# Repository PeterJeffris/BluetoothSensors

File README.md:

Background:
The goal of this project is to create an sensor platform wirelessly connected to a control and logging application on an android phone. The sensors include an accelerometer, a gyroscope, a combined barometer and temperature sensor and an ambient light sensor. The data is logged to the phones internal SD card or simply shown on the screen set with GUI configuration buttons on the android phone.

Software Development:
There are 3 collections of software developed for this project. The first is the java code for the android phone residing in the android folder. This code is intended to be compiled and uploaded to the phone using the android SDK package in the Eclipse IDE. This code contains a multithreaded android application that manages the display and configuration options in one group of threads and receives and processes and logs the data received over the Bluetooth radio connection in the other set.

The second collection of code is written in C++ and is used to run the Atmega328 chip that coordinates the collection of data from the sensors and is found in the AVR folder. This code is meant to be used with the wiring libraries and can be uploaded via the Arduino IDE or a build program such as scons or make. I2C driver libraries were written for this application to communicate with each of the sensors and are also included in this folder. Additionally there is a test script written in python that allows direct collection from the senor board by hooking up an FTDI cable to the Tx and Rx lines of the radio.

The final code is written in matlab and is used to determine the calibration coefficients for the relative alignment and scaling of the accelerometer and gyroscope. There are also several functions written to perform conversions between Euler angles which the gyroscope returns and rotation matrix and quaternion representations.

Hardware Development:
The circuit schematics and PCB layout are present in the hardware folder. These files are mean to be developed with the Eagle CAD software. The board itself is constructed as an Arduino compatible shield and matches directly with the pins on an Arduino board. Each of the sensors was purchased on breakout boards from sparkfun allowing for through hole construction techniques using chemically etched boards. 

A solder jumper had to be modified on the bottom of the gyroscope boards in order to change their output from SPI to I2C. Along with the gyroscope, the accelerometer and barometer also use the I2C communication protocol. Theses chips are placed on a single BUS with 3.3 Volt logic. This logic is then converted to 5 volt logic to the AVR processor using a level shifting circuit. The power supply utilizes 4 AA alkaline batteries whose voltage begins at 5.6 volts and drops to 4 volts at 4 discharge. The linear regulator supply filters and regulates this voltage at the cost of a 1 volt drop out. The AVR processor and radio are tolerant to the voltage changes down to the point where the batteries are operating at 4 volts. 

To configure the radio it must be connected to an FTDI cable. Open a serial terminal using the FTDI port (the arduino IDE serial monitor will also work if you select the FTDI port) and disable the line ending on output and send the string '$$$' (everything inside '' is entered and return is pressed). You will see the radio enter command mode by returning 'CMD' if you have done the setup correctly and the status light will blink at a faster interval. Then re-enable line endings and send the command 'SN,DEVICE_NAME' where DEVICE_NAME is what you want the bluetooth device name to be displayed as. Use the command 'SP,XXXX' to set the security pin where XXXX is the alphanumeric pin code to be entered upon connecting to the device from a phone. Use the command 'SU,XX' to set the baud rate where the XX is the first two characters of the baud rate (ie 11 -> 115000 bits per second). If this is done the corresponding baud rate in the AVR code also needs to be changed. To verify this information has been properly set use the 'D' command to display the basic settings. 

Features: 
The slides included in this repository describe the various features of the system and show the conclusions of the experimental trials utilizing the sensor.

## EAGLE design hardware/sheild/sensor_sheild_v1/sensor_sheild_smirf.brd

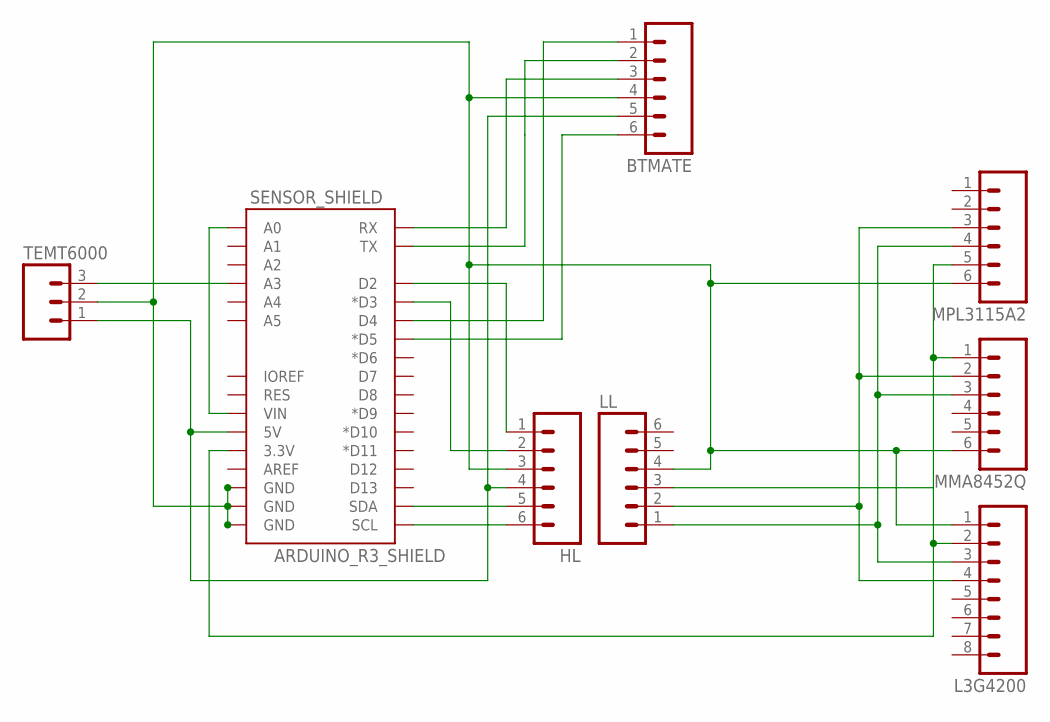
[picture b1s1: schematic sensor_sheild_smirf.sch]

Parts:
BTMATE: M06NO_SILK; 1X06_NO_SILK
HL: M06SIP; 1X06
L3G4200: M08; 1X08_PIN1_NO_SILK
LL: M06SIP; 1X06
MMA8452Q: M06SIP; 1X06
MPL3115A2: M06SIP; 1X06
SENSOR_SHIELD: ARDUINO_R3_SHIELD; UNO_R3_SHIELD
TEMT6000: M031X03_NO_SILK; 1X03_NO_SILK

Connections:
GND: BTMATE.4, HL.3, L3G4200.1, LL.4, MMA8452Q.6, MPL3115A2.6, SENSOR_SHIELD.GND@0 (GND), SENSOR_SHIELD.GND@1 (GND), SENSOR_SHIELD.GND@2 (GND), TEMT6000.2
unnamed: SENSOR_SHIELD.A0, SENSOR_SHIELD.VIN
unnamed: BTMATE.2, SENSOR_SHIELD.TX
unnamed: BTMATE.3, SENSOR_SHIELD.RX
unnamed: BTMATE.1, SENSOR_SHIELD.D4
unnamed: BTMATE.6, SENSOR_SHIELD.D5 (*D5)
unnamed: L3G4200.4, LL.2, MMA8452Q.2, MPL3115A2.3
unnamed: HL.2, SENSOR_SHIELD.D3 (*D3)
unnamed: HL.1, SENSOR_SHIELD.D2
unnamed: L3G4200.3, LL.1, MMA8452Q.3, MPL3115A2.4
unnamed: HL.5, SENSOR_SHIELD.SDA
unnamed: BTMATE.5, HL.4, SENSOR_SHIELD.5V, TEMT6000.1
unnamed: L3G4200.2, LL.3, MMA8452Q.1, MPL3115A2.5, SENSOR_SHIELD.3.3V
unnamed: HL.6, SENSOR_SHIELD.SCL
unnamed: SENSOR_SHIELD.A3, TEMT6000.3

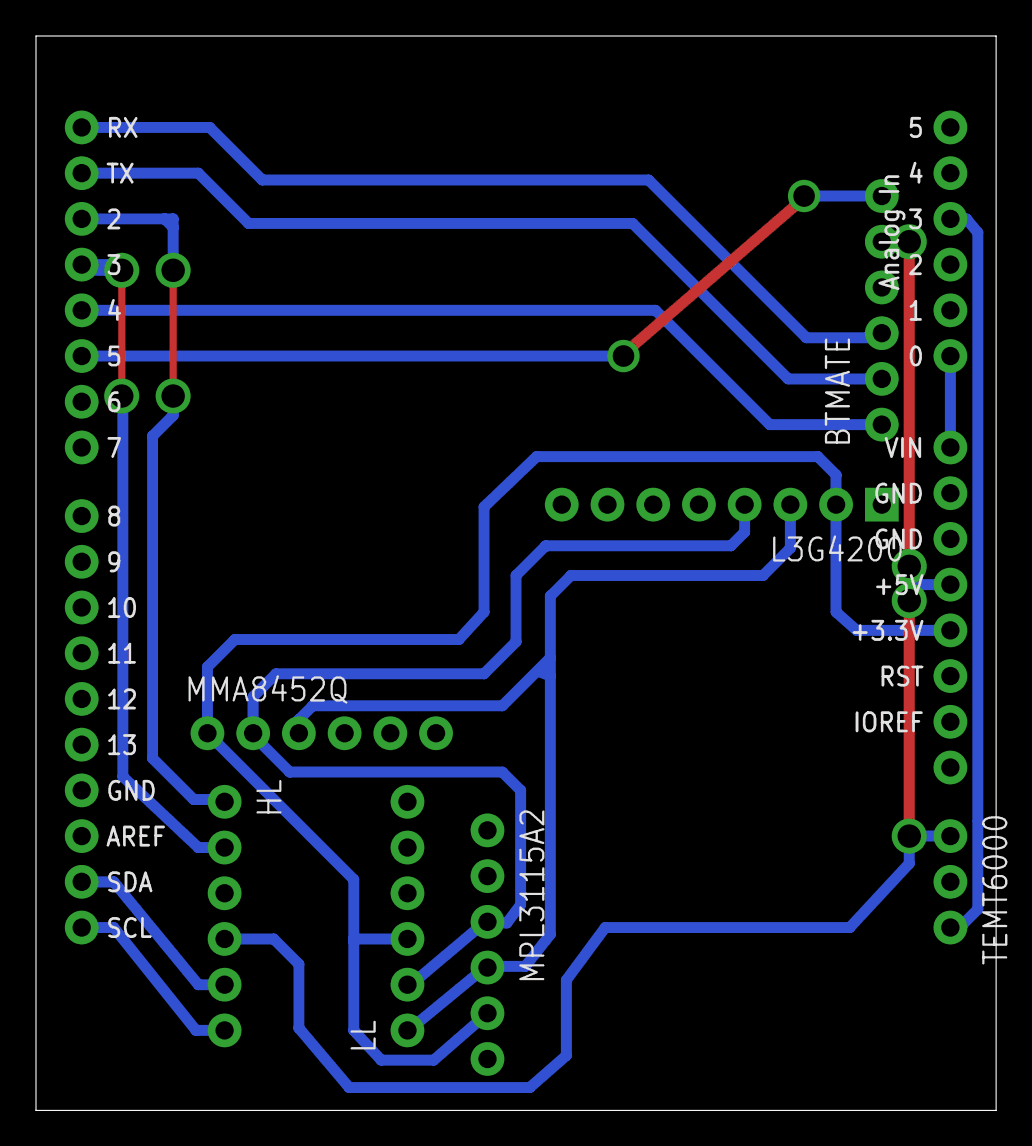
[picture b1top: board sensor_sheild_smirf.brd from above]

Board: 2 copper layers, 53.3 x 59.7 mm, 8 parts (0 on the bottom side), 15 nets.

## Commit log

2014-08-18 Bluetooth Sensors Project

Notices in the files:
parts and their libraries:
SparkFun-Boards: Licensing: Creative Commons ShareAlike 4.0 International - https://creativecommons.org/licenses/by-sa/4.0
